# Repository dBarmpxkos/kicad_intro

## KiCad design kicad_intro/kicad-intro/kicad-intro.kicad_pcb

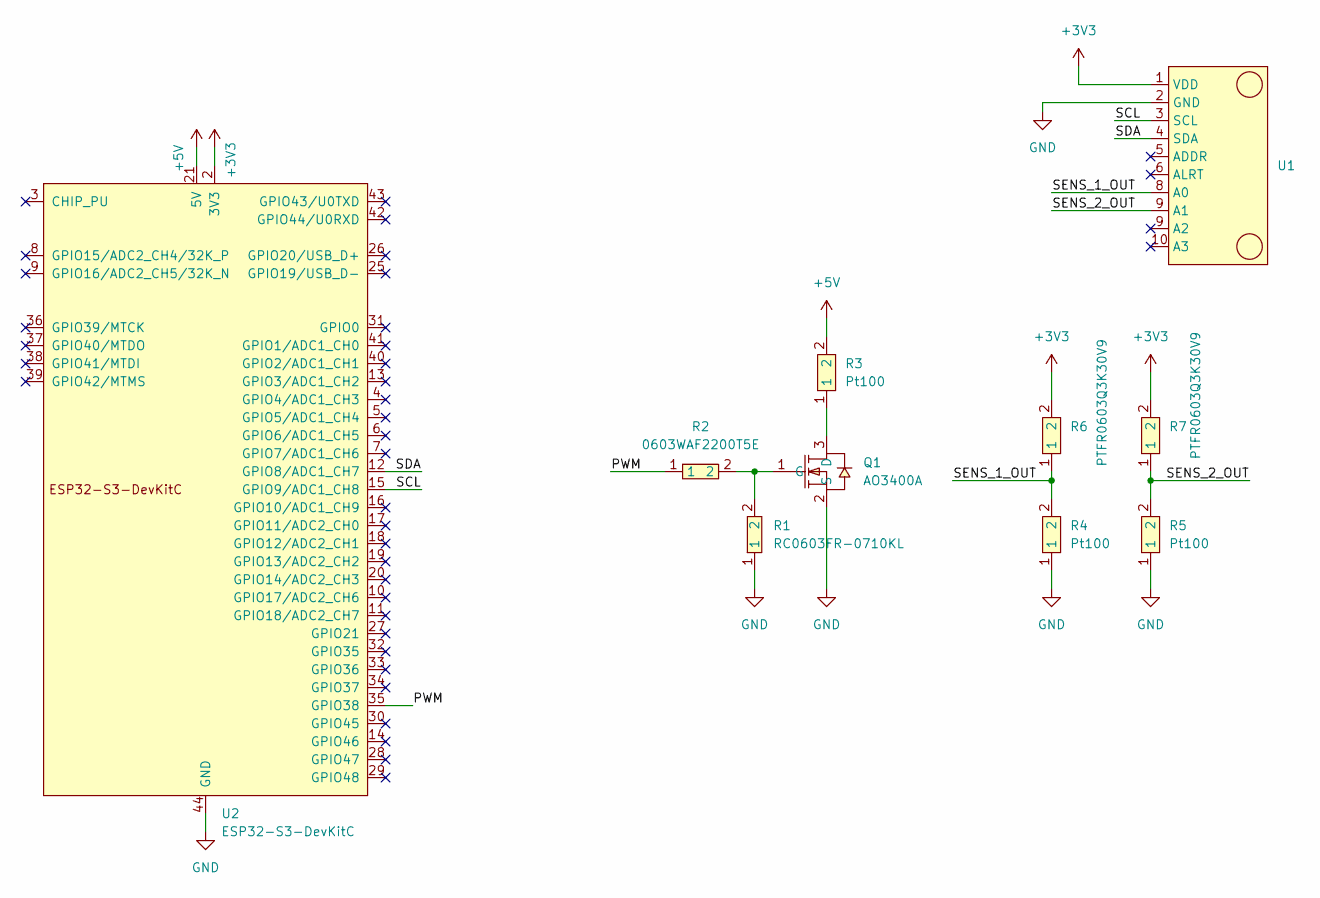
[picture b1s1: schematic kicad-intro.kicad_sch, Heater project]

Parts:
Q1: AO3400A; SOT-23-3_L2.9-W1.3-P1.90-LS2.4-BR; MPN AO3400A; LCSC Part C20917
R1: RC0603FR-0710KL; R0603; MPN RC0603FR-0710KL; LCSC Part C98220
R2: 0603WAF2200T5E; R0603; MPN 0603WAF2200T5E; LCSC Part C22962
R3, R4, R5: Pt100; R0603
R6, R7: PTFR0603Q3K30V9; R0603; MPN PTFR0603Q3K30V9; LCSC Part C19691413
U1: ADS1115
U2: ESP32-S3-DevKitC

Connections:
+3V3: R6.2, R7.2, U1.1 (VDD), U2.1 (3V3), U2.2 (3V3)
+5V: R3.2, U2.21 (5V)
/PWM: R2.1, U2.35 (GPIO38)
/SCL: U1.3 (SCL), U2.15 (GPIO9/ADC1_CH8)
/SDA: U1.4 (SDA), U2.12 (GPIO8/ADC1_CH7)
/SENS_1_OUT: R4.2, R6.1, U1.8 (A0)
/SENS_2_OUT: R5.2, R7.1, U1.9 (A1)
GND: Q1.2 (S), R1.1, R4.1, R5.1, U1.2 (GND), U2.22 (GND), U2.23 (GND), U2.24 (GND), U2.44 (GND)
unnamed: Q1.3 (D), R3.1
unnamed: Q1.1 (G), R1.2, R2.2

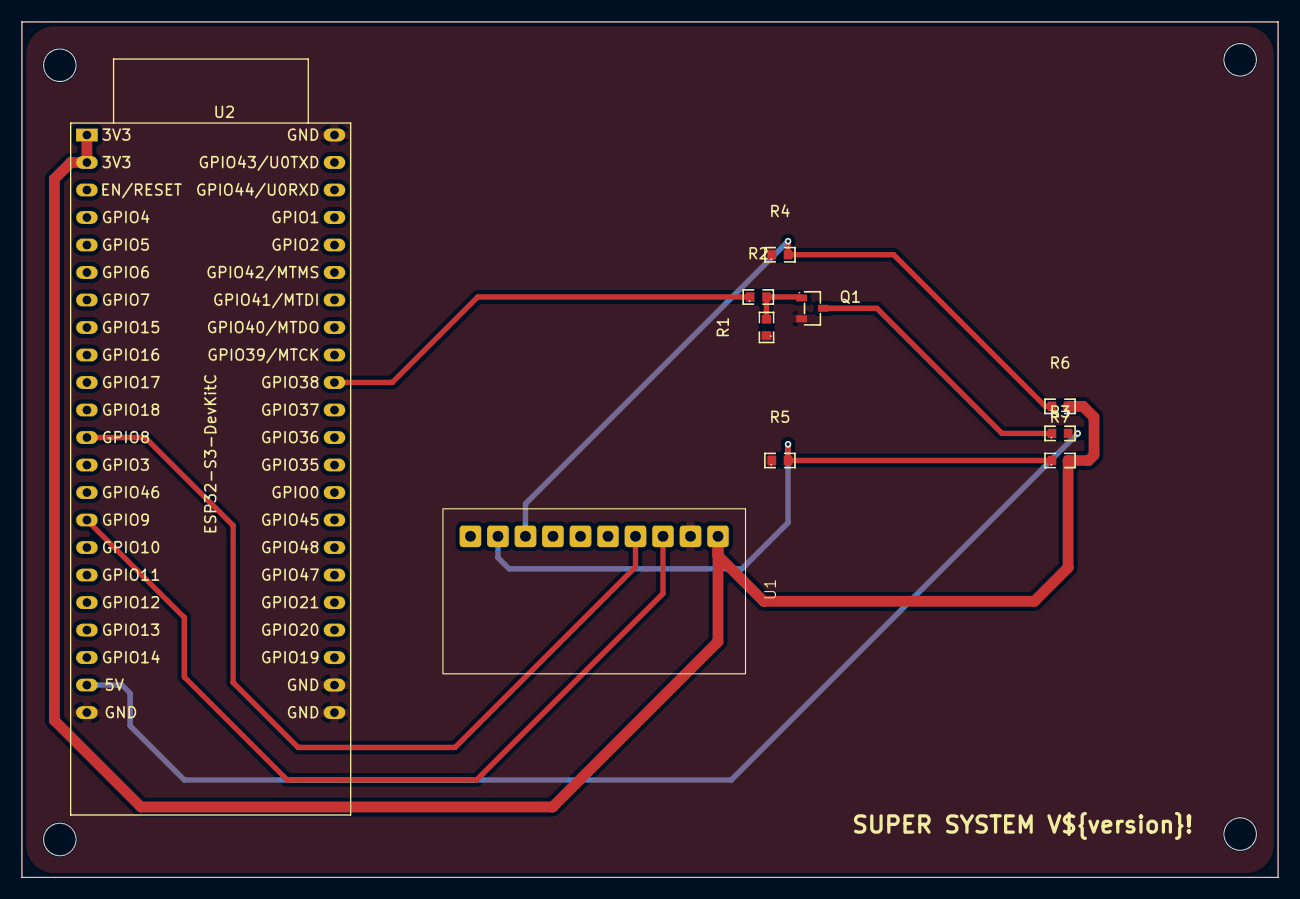
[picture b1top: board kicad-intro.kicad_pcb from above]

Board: 2 copper layers, 116.0 x 79.0 mm, 10 parts (0 on the bottom side), 10 nets.
